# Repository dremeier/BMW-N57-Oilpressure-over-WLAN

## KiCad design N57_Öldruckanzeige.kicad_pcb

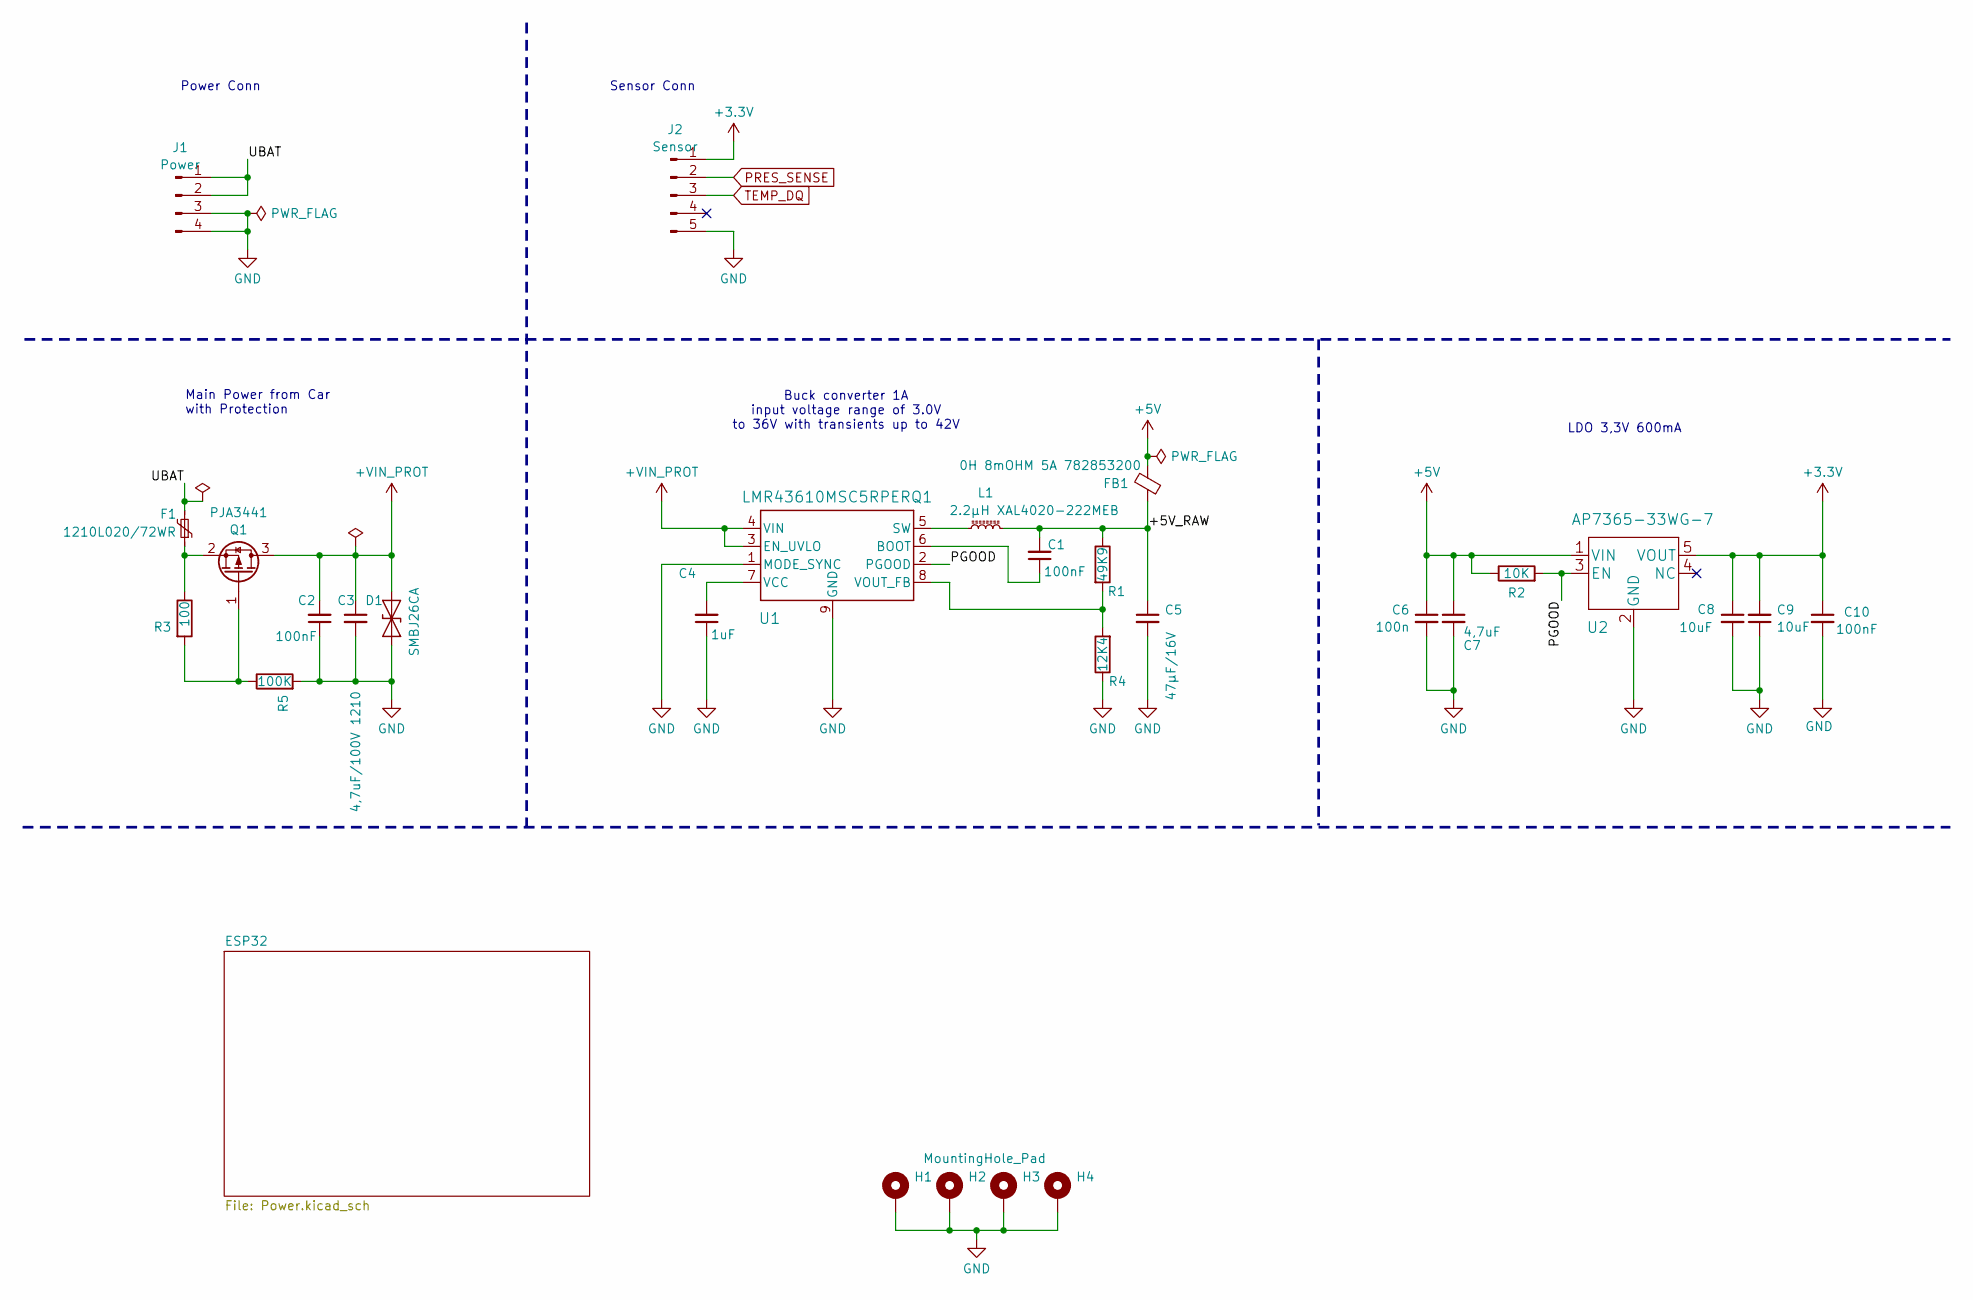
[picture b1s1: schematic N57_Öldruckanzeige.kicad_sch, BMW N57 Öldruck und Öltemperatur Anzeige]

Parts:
C1, C2, C10: 100nF; C_0603_1608Metric_Pad1.08x0.95mm_HandSolder
C3: 4,7uF/100V 1210; C_0603_1608Metric_Pad1.08x0.95mm_HandSolder
C4: 1uF; C_0603_1608Metric_Pad1.08x0.95mm_HandSolder
C5: 47µF/16V; C_1210_3225Metric_Pad1.33x2.70mm_HandSolder
C6: 100n; C_0603_1608Metric_Pad1.08x0.95mm_HandSolder
C7: 4,7uF; C_0805_2012Metric_Pad1.18x1.45mm_HandSolder
C8, C9: 10uF; C_0805_2012Metric_Pad1.18x1.45mm_HandSolder
D1: SMBJ26CA; D_SMA
F1: 1210L020/72WR; Fuse_1210_3225Metric
FB1: 0H 8mOHM 5A 782853200; L_Eaton_MCL2012V1
H1, H2, H3, H4: MountingHole_Pad; MountingHole_3.2mm_M3_ISO7380_Pad
J1: Power; JST_PH_S4B-PH-K_1x04_P2.00mm_Horizontal
J2: Sensor; JST_PH_S5B-PH-K_1x05_P2.00mm_Horizontal
L1: 2.2µH XAL4020-222MEB; L_Coilcraft_XxL4040
Q1: PJA3441; SOT-23-3
R1: 49K9; R_0603_1608Metric_Pad0.98x0.95mm_HandSolder
R2: 10K; R_0603_1608Metric_Pad0.98x0.95mm_HandSolder; Digi-Key_PN 311-10KGRCT-ND
R3: 100; R_0603_1608Metric_Pad0.98x0.95mm_HandSolder
R4: 12K4; R_0603_1608Metric_Pad0.98x0.95mm_HandSolder
R5: 100K; R_0603_1608Metric_Pad0.98x0.95mm_HandSolder
U1: LMR43610MSC5RPERQ1; RPE0009A-MFG
U2: AP7365-33WG-7; SOT-23-5_HandSoldering; Digi-Key_PN AP2112K-3.3TRG1DICT-ND

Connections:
+3.3V: C8.1, C9.2, C10.1, J2.1, U2.5 (VOUT); also elsewhere on the board
+5V: C6.1, C7.1, FB1.2, R2.1, U2.1 (VIN); also elsewhere on the board
+VIN_PROT: C2.2, C3.1, D1.2 (A2), Q1.3 (D), U1.3 (EN_UVLO), U1.4 (VIN)
/+5V_RAW: C1.2, C5.1, FB1.1, L1.2, R1.1
/PGOOD: R2.2, U1.2 (PGOOD), U2.3 (EN)
/UBAT: F1.2, J1.1, J1.2
GND: C2.1, C3.2, C4.1, C5.2, C6.2, C7.2, C8.2, C9.1, C10.2, D1.1 (A1), H1.1, H2.1, H3.1, H4.1, J1.3, J1.4, J2.5, R4.1, R5.2, U1.1 (MODE_SYNC), U1.9 (GND), U2.2 (GND); also elsewhere on the board
unnamed: Q1.1 (G), R3.2, R5.1
unnamed: F1.1, Q1.2 (S), R3.1
unnamed: C1.1, U1.6 (BOOT)
unnamed: L1.1, U1.5 (SW)
unnamed: C4.2, U1.7 (VCC)
unnamed: R1.2, R4.2, U1.8 (VOUT_FB)
PRES_SENSE: J2.2; also elsewhere on the board
TEMP_DQ: J2.3; also elsewhere on the board

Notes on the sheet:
Sensor Conn
Main Power from Car with Protection
Power Conn
LDO 3,3V 600mA
Buck converter 1A input voltage range of 3.0V to 36V with transients up to 42V

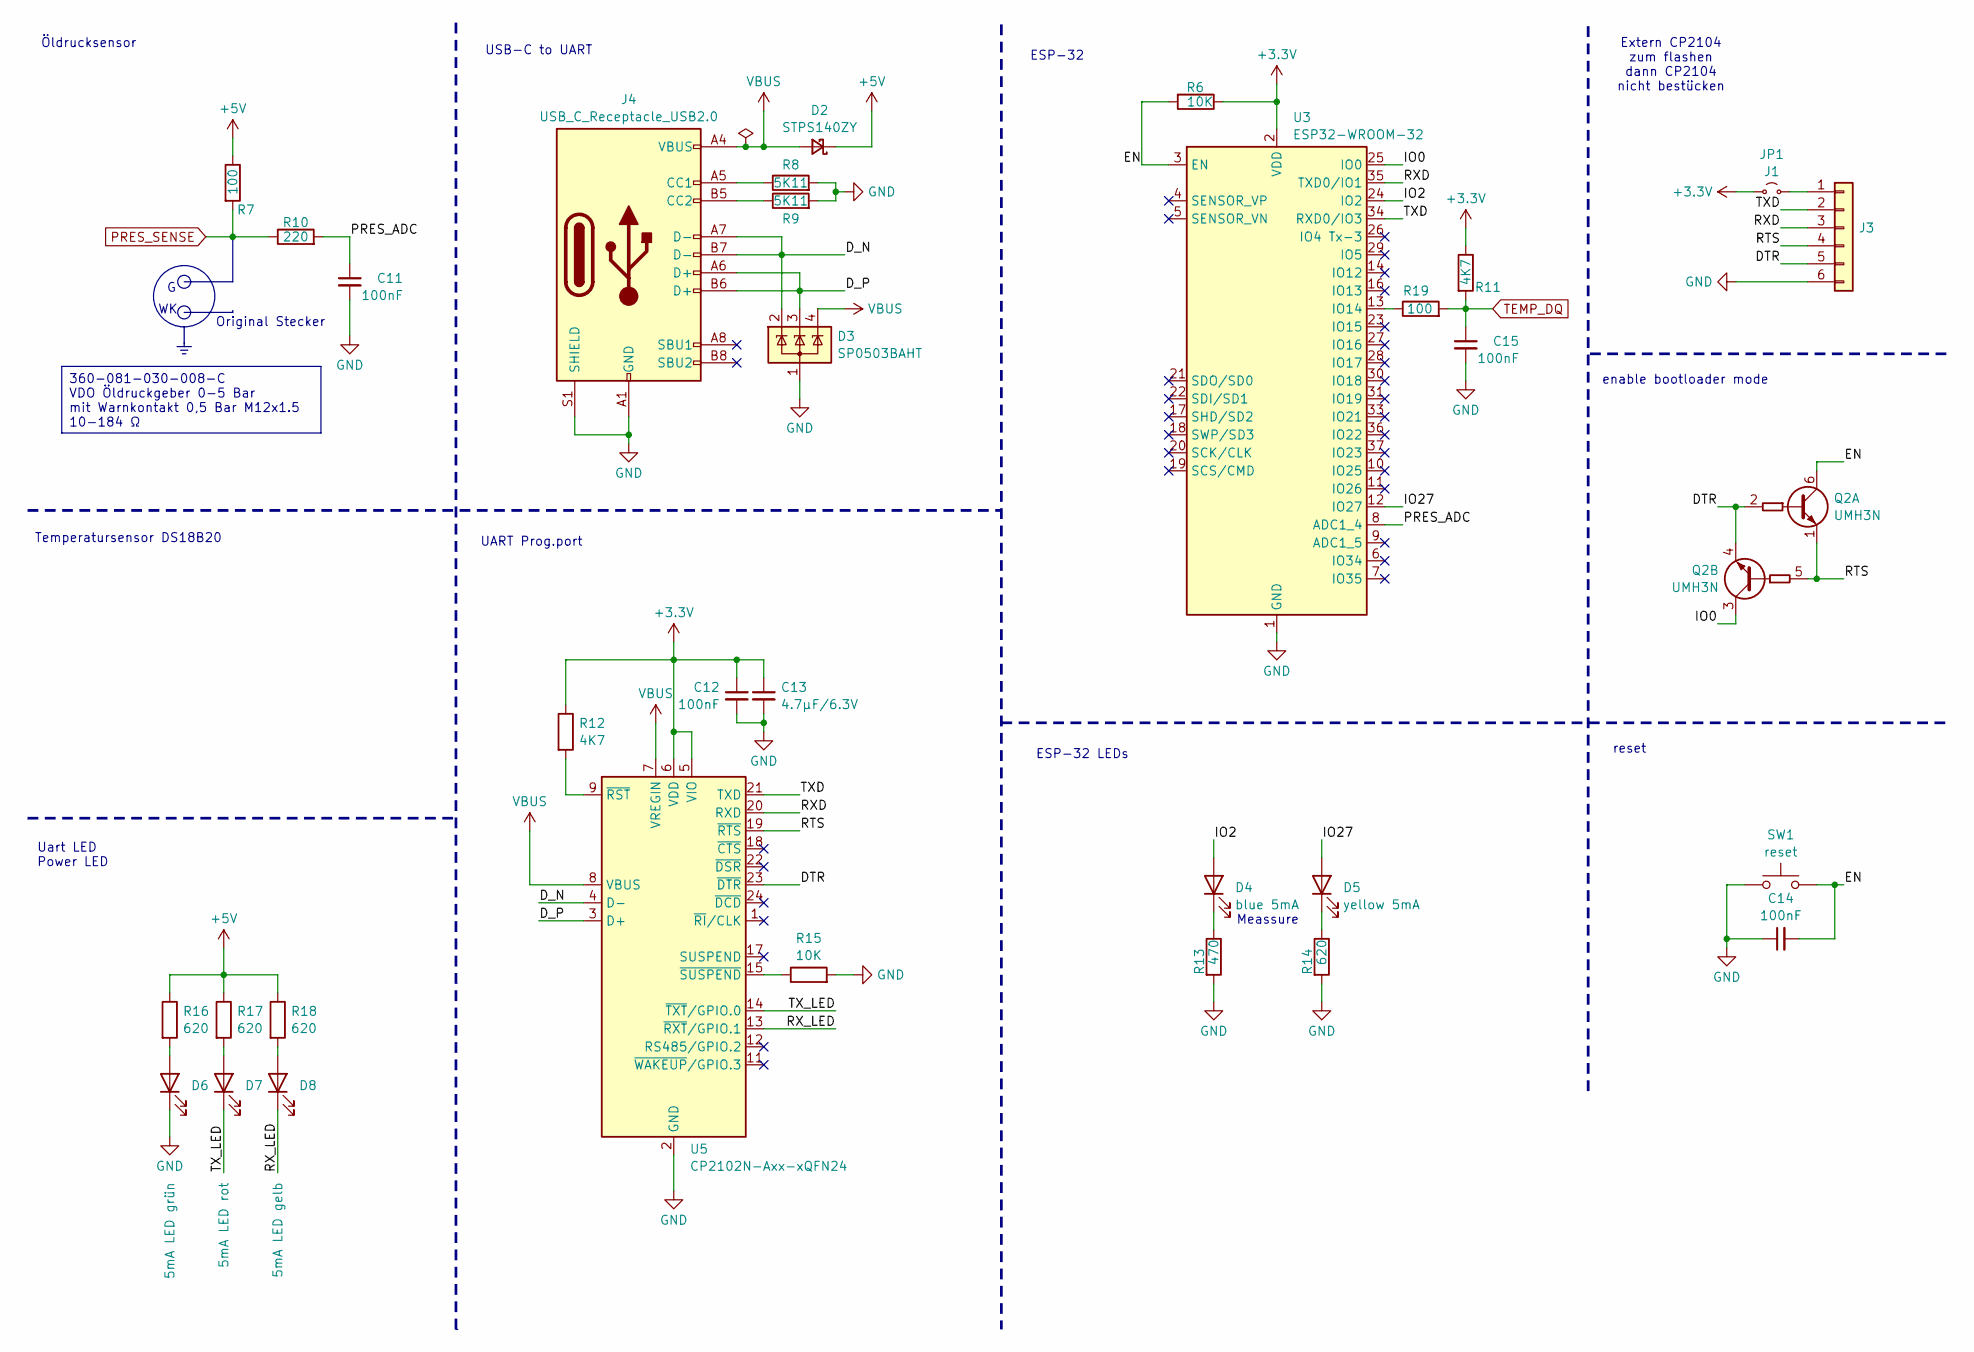
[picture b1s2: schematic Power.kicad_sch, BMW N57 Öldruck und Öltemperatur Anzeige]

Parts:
C11, C12, C14, C15: 100nF; C_0603_1608Metric_Pad1.08x0.95mm_HandSolder
C13: 4.7μF/6.3V; C_0603_1608Metric_Pad1.08x0.95mm_HandSolder
D2: STPS140ZY; D_SOD-123
D3: SP0503BAHT; SOT-143
D4: blue 5mA; LED_0603_1608Metric_Pad1.05x0.95mm_HandSolder
D5: yellow 5mA; LED_0603_1608Metric_Pad1.05x0.95mm_HandSolder
D6: 5mA LED grün; LED_0603_1608Metric_Pad1.05x0.95mm_HandSolder
D7: 5mA LED rot; LED_0603_1608Metric_Pad1.05x0.95mm_HandSolder
D8: 5mA LED gelb; LED_0603_1608Metric_Pad1.05x0.95mm_HandSolder
J3: Conn_01x03; JST_PH_B6B-PH-K_1x06_P2.00mm_Vertical
J4: USB_C_Receptacle_USB2.0; USB_C_Receptacle_GCT_USB4105-xx-A_16P_TopMnt_Horizontal
JP1: J1; PinSocket_1x05_P2.54mm_Vertical
Q2: UMH3N; SOT-363_SC-70-6
R6, R15: 10K; R_0603_1608Metric_Pad0.98x0.95mm_HandSolder
R7: 100; R_1206_3216Metric
R8, R9: 5K11; R_0603_1608Metric_Pad0.98x0.95mm_HandSolder
R10: 220; R_0603_1608Metric_Pad0.98x0.95mm_HandSolder
R11, R12: 4K7; R_0603_1608Metric_Pad0.98x0.95mm_HandSolder
R13: 470; R_0603_1608Metric_Pad0.98x0.95mm_HandSolder
R14, R16, R17, R18: 620; R_0603_1608Metric_Pad0.98x0.95mm_HandSolder
R19: 100; R_0603_1608Metric_Pad0.98x0.95mm_HandSolder
SW1: reset; SW_Push_1P1T_NO_Vertical_Wuerth_434133025816
U3: ESP32-WROOM-32
U5: CP2102N-Axx-xQFN24; QFN-24-1EP_4x4mm_P0.5mm_EP2.6x2.6mm

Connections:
+3.3V: C12.1, C13.1, JP1.1 (A), R6.1, R11.1, R12.1, U3.2 (VDD), U5.5 (VIO), U5.6 (VDD); also elsewhere on the board
+5V: D2.1 (K), R7.1, R16.1, R17.1, R18.1; also elsewhere on the board
/ESP32/DTR: J3.5, Q2.2 (B1), Q2.4 (E2), U5.23 (~DTR)
/ESP32/D_N: D3.2 (K), J4.A7 (D-), J4.B7 (D-), U5.4 (D-)
/ESP32/D_P: D3.3 (K), J4.A6 (D+), J4.B6 (D+), U5.3 (D+)
/ESP32/EN: C14.2, Q2.6 (C1), R6.2, SW1.2, U3.3 (EN)
/ESP32/IO0: Q2.3 (C2), U3.25 (IO0)
/ESP32/IO2: D4.2 (A), U3.24 (IO2)
/ESP32/IO27: D5.2 (A), U3.12 (IO27)
/ESP32/PRES_ADC: C11.1, R10.2, U3.8 (ADC1_4)
/ESP32/RTS: J3.4, Q2.1 (E1), Q2.5 (B2), U5.19 (~RTS)
/ESP32/RXD: J3.3, U3.35 (TXD0/IO1), U5.20 (RXD)
/ESP32/RX_LED: D8.1 (K), U5.13 (~RXT/GPIO.1)
/ESP32/TXD: J3.2, U3.34 (RXD0/IO3), U5.21 (TXD)
/ESP32/TX_LED: D7.1 (K), U5.14 (~TXT/GPIO.0)
GND: C11.2, C12.2, C13.2, C14.1, C15.2, D3.1 (A), D6.1 (K), J3.6, J4.A1 (GND), J4.A12 (GND), J4.B1 (GND), J4.B12 (GND), J4.S1 (SHIELD), R8.2, R9.2, R13.2, R14.2, R15.2, SW1.1, U3.1 (GND), U3.15 (GND), U3.38 (GND), U3.39 (GND), U5.2 (GND), U5.25 (GND); also elsewhere on the board
unnamed: D4.1 (K), R13.1
unnamed: D5.1 (K), R14.1
unnamed: D6.2 (A), R16.2
unnamed: D7.2 (A), R17.2
unnamed: D8.2 (A), R18.2
unnamed: J3.1, JP1.2 (B)
unnamed: J4.A5 (CC1), R8.1
unnamed: J4.B5 (CC2), R9.1
unnamed: R19.1, U3.13 (IO14)
unnamed: R12.2, U5.9 (~RST)
unnamed: R15.1, U5.15 (~SUSPEND)
PRES_SENSE: R7.2, R10.1; also elsewhere on the board
TEMP_DQ: C15.1, R11.2, R19.2; also elsewhere on the board
VBUS: D2.2 (A), D3.4 (K), J4.A4 (VBUS), J4.A9 (VBUS), J4.B4 (VBUS), J4.B9 (VBUS), U5.7 (VREGIN), U5.8 (VBUS)

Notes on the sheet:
Meassure
Temperatursensor DS18B20
reset
ESP-32
enable bootloader mode
UART Prog.port
ESP-32 LEDs
Original Stecker
Öldrucksensor
Extern CP2104 zum flashen dann CP2104 nicht bestücken
Uart LED Power LED
USB-C to UART
360-081-030-008-C VDO Öldruckgeber 0-5 Bar mit Warnkontakt 0,5 Bar M12x1.5 10-184 Ω

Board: 2 copper layers, 60 parts (0 on the bottom side), 40 nets, no tracks yet.
